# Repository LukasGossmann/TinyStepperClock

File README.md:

**Description:**  
Tiny stepper motor based clock (including base, L=80mm, W=80mm, H=127mm)  
The clock face is 50mm in diameter with a 5mm wide clear / slightly opaque ring around it for a total diameter of 60mm.  
Behind the clock face is an LED ring with 12 WS2812 LEDs that light up every hour and play a short animation.  
The stepper motors used in this clock are very weak so a lot of care need to be taken to align the shafts properly and for the gears to be running as true as possible on the shafts.  
Each stepper motor has 20 fullsteps per revolution which with a gear reduction of 3:1 gives 60 steps per revolution.  
The minute hand takes a step every minute while the hour hand takes a step every 12 minutes.  
Since this is the tiny version that implies the existence of a bigger stepper motor based clock.
The bigger version can be found here: [StepperClock](https://github.com/LukasGossmann/StepperClock)  
**Waring:** The clock is mains powered and there are a few somewhat exposed live traces / metal contacts so build and use at your own risk.

**Building:**  
Create all parts needed as shown in the FreeCAD drawing.  
Assemble as shown on the pictures and in the FreeCAD drawing.  
A lot of care needs to be taken to be as precise as possible as there isn't much room for tolerance in this design due to the weak motors and tiny gears.  
Also a lot of parts are press fit together (bearings in holders, motors in holders, clock face in clear ring, clear ring on LED ring, etc.) so make sure to adjust the design to fit the expacted tolerances of your manufacturing process and the parts you bought.
Note that one of the stepper motors is wired in the opposite direction so that the same step sequence can be used to drive them.  
If the motors are turning in the wrong direction or both motors were wired the same on accident the code allows for inverting the motor direction as well.
When attaching the clock hands to the shaft the clock needs to be powered on (preferably through usb).  
That way the stepper motors align with one of their magnetic steps which ensures that the hands can properly point to all positions they need to.
Align the clock hands with the 12 o'clock position and solder them in place.

**Tools:**
- **CNC machine** or other way to create parts from a piece of flat material as well as for engraving the clock face.
- **FDM or SLA printer** to create the spacer and the clear ring.
- Depending on the parts you can get and the need to modify them a **lathe** is very useful.
- Soldering iron, screwdrivers, etc.

**Stepper motors:**  
20 steps per rev  
3.3V @ 80mA per coil (gets slightly warm)  
Does not like having both coils energized at the same time, gets pretty hot and doesn't step well  
Diameter: 8mm  
Length: 9.2mm  
Gear (from factory): 10 teeth 0.2 module? (2.3mm diameter)  
Can be found from multiple sellers in china for very cheap (AliExpress)

**Stepper driver:**  
DRV8833 without current limiting (3.3V straight through)  
On a breakout board just soldered onto carrier PCB

**Clock hands:**  
Need to be made of a material that can be soldered to so they can be attached to the shafts.  
CNC milling them from some leftover PCB material works great.

**Power supply:**  
The Pi Pico is powered from a 230V to 5V mains power supply "brick" made by Hi-Link which can supply 600mA.  
To power the stepper drivers the 3.3V output of the Pi Pico is used. 
The stepper motors together draw around 160mA at 3.3V with only one of their coils being active at a time.

**Needed parts (mechanical):**
- 2x 60 tooth gear, 1.4mm thick, 0.3 module
    - one with 4mm hole and one with 2mm hole for the shaft
- 2x 20 tooth gear, 1.4mm thick, 0.3 module
    - with 2.3mm hole to fit onto factory gear of the stepper motor
- 2x Bearing 8mm OD, 4mm ID, 3mm thick
- 1x Bearing 7.3mm OD, 2mm ID, 3mm thick
    - 7mm OD bearings are also available, pick whatever is cheaper and modify the bearing holder design to fit your needs
- 3mm thick material for the frame parts (I used Resopal)
- Brass tube 4mm OD, 2mm ID (shaft for the hour hand)
- Brass tube 5mm OD, 3mm ID (used as spacers for the stacked PCBs)
- Brass rod 2mm (shaft for the minute hand)
- Various M2 and M3 screws, nuts and washers
- A block of wood or other material to make a base for the clock

**Needed parts (electrical):**
- 2x Stepper motor
    - order more than that because they tend to arrive broken (coil wires ripped off)
- 1x Raspberry Pi Pico without headers
- 1x 5V PSU (Hi-Link HLK-PM01 or pin and size compatible)
- 1x WS2812 LED ring with 12 LEDS (~50mm OD)
    - 8 LED version (~32mm OD) should work too with a modified spacer and a few code changes
- 1x Diode (shotkey or any other type, 1N4007 works just fine)
- 1x Capacitor (At least 5V rating, around 470µF works fine)
- 1x 2.54mm 2 pin screw terminal
- Some 2.54mm pin headers
- Thin wires
- The PCBs from the KiCAD project

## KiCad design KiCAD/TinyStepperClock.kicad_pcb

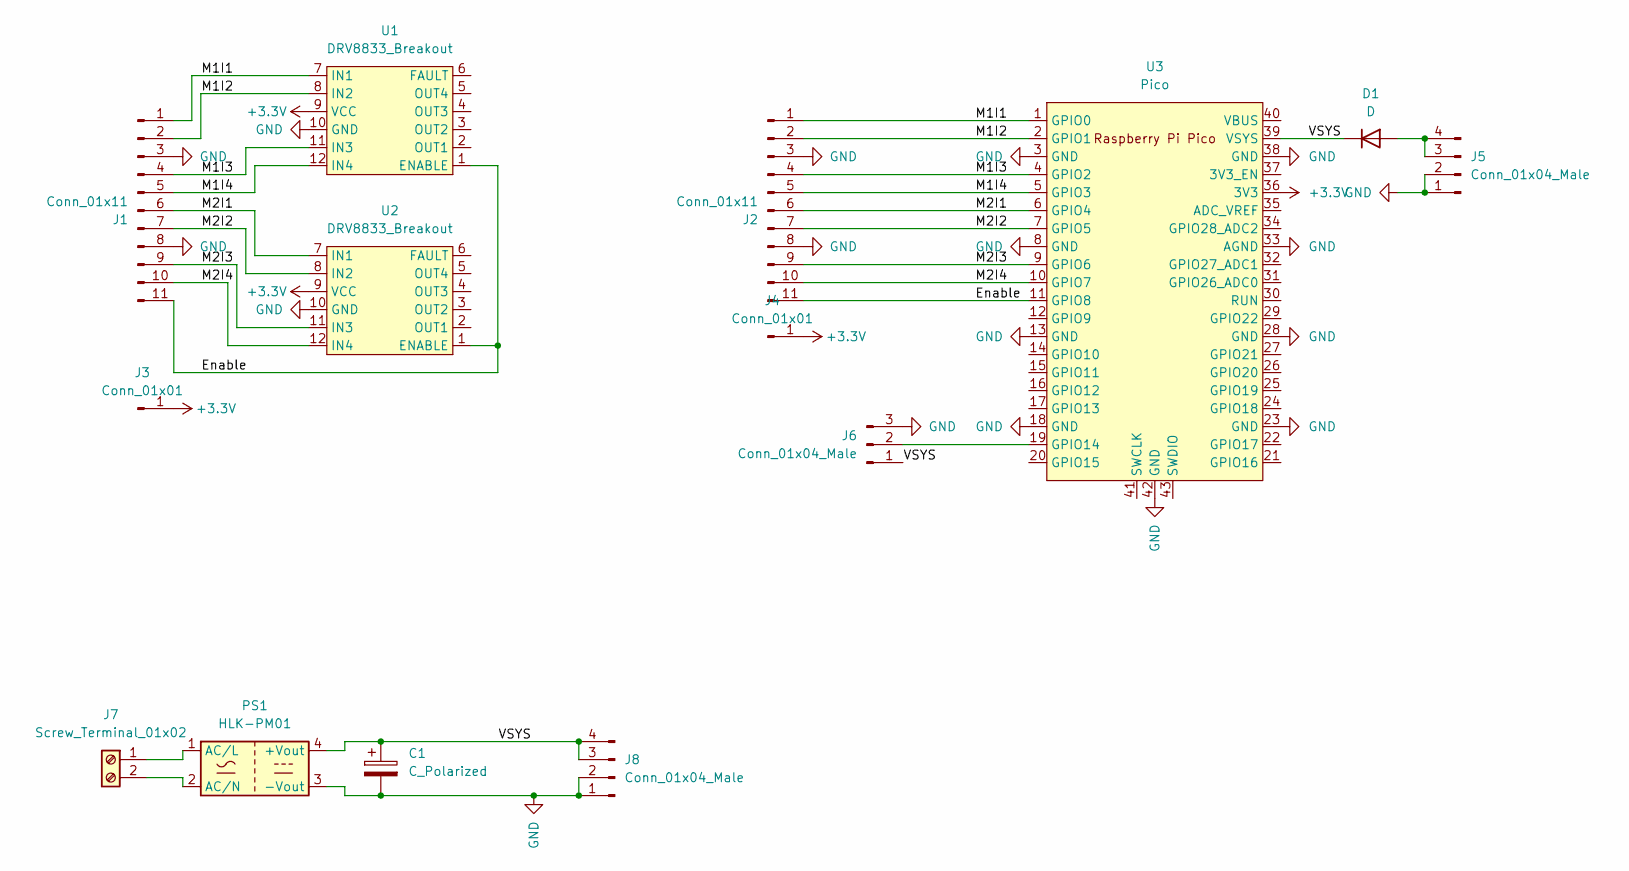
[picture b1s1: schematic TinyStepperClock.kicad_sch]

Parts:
C1: C_Polarized; CP_Radial_D10.0mm_P5.00mm_P7.50mm
D1: D; D_DO-15_P12.70mm_Horizontal
J1, J2: Conn_01x11; PinHeader_1x11_P2.54mm_Vertical
J3, J4: Conn_01x01; PinHeader_1x01_P2.54mm_Vertical
J5: Conn_01x04_Male; PinHeader_1x04_P2.54mm_Vertical
J6: Conn_01x04_Male; PinHeader_1x03_P2.54mm_Horizontal
J7: Screw_Terminal_01x02; TerminalBlock_Phoenix_MKDS-1,5-2-5.08_1x02_P5.08mm_Horizont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
J8: Conn_01x04_Male; PinSocket_1x04_P2.54mm_Vertical
PS1: HLK-PM01; Converter_ACDC_HiLink_HLK-PMxx
U1, U2: DRV8833_Breakout
U3: Pico; RPi_Pico_SMD_TH

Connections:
+3.3V: J3.1, J4.1, U1.9 (VCC), U2.9 (VCC), U3.36 (3V3)
/Enable: J1.11, J2.11, U1.1 (ENABLE), U2.1 (ENABLE), U3.11 (GPIO8)
/M1I1: J1.1, J2.1, U1.7 (IN1), U3.1 (GPIO0)
/M1I2: J1.2, J2.2, U1.8 (IN2), U3.2 (GPIO1)
/M1I3: J1.4, J2.4, U1.11 (IN3), U3.4 (GPIO2)
/M1I4: J1.5, J2.5, U1.12 (IN4), U3.5 (GPIO3)
/M2I1: J1.6, J2.6, U2.7 (IN1), U3.6 (GPIO4)
/M2I2: J1.7, J2.7, U2.8 (IN2), U3.7 (GPIO5)
/M2I3: J1.9, J2.9, U2.11 (IN3), U3.9 (GPIO6)
/M2I4: J1.10, J2.10, U2.12 (IN4), U3.10 (GPIO7)
/VSYS: C1.1, D1.1 (K), J6.1, J8.3, J8.4, PS1.4 (+Vout), U3.39 (VSYS)
GND: C1.2, J1.3, J1.8, J2.3, J2.8, J5.1, J5.2, J6.3, J8.1, J8.2, PS1.3 (-Vout), U1.10 (GND), U2.10 (GND), U3.3 (GND), U3.8 (GND), U3.13 (GND), U3.18 (GND), U3.23 (GND), U3.28 (GND), U3.33 (AGND), U3.38 (GND), U3.42 (GND)
unnamed: D1.2 (A), J5.3, J5.4
unnamed: J6.2, U3.19 (GPIO14)
unnamed: J7.1, PS1.1 (AC/L)
unnamed: J7.2, PS1.2 (AC/N)

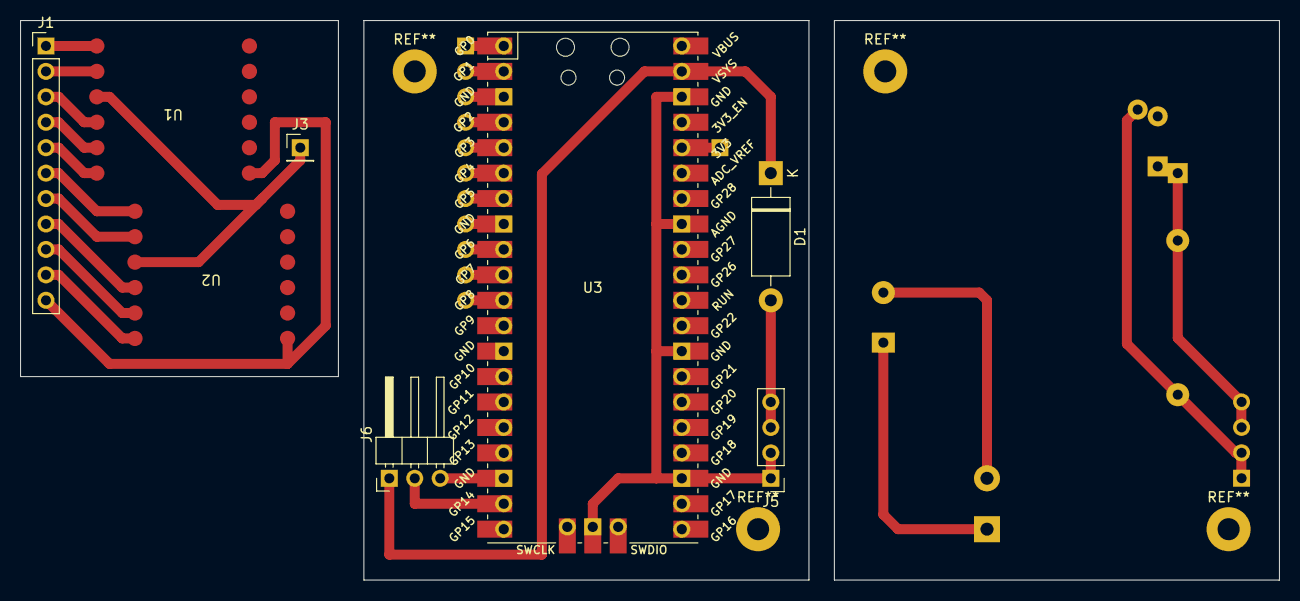
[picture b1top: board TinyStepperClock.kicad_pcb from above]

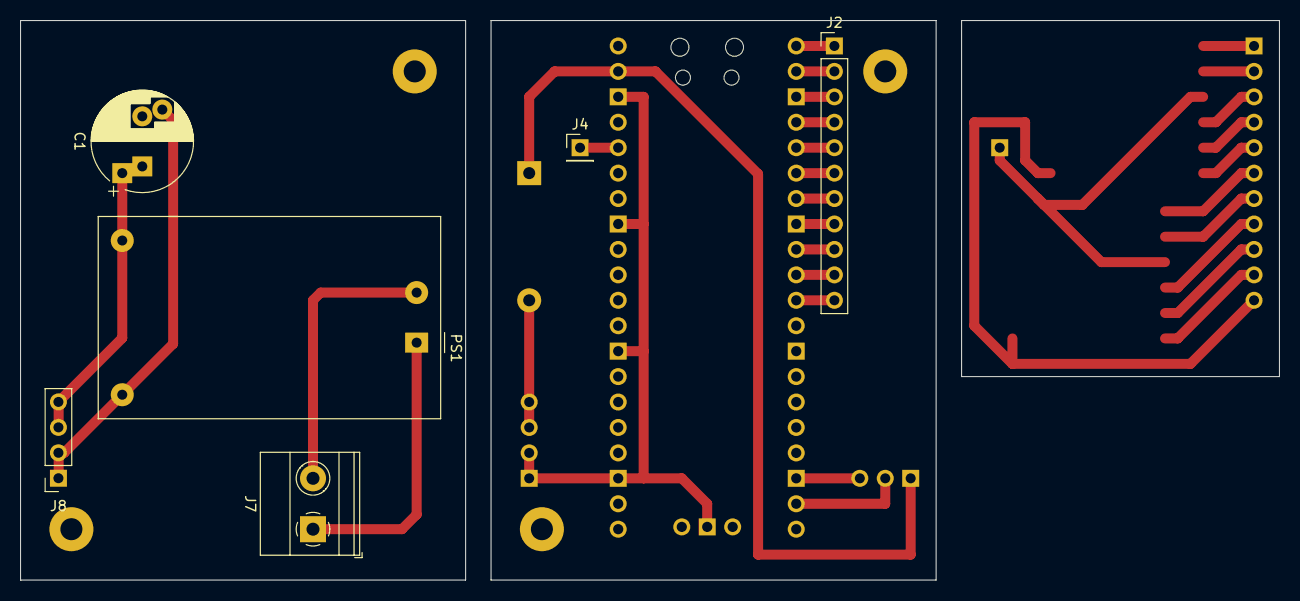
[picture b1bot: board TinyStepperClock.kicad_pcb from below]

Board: 2 copper layers, 125.7 x 55.9 mm, 14 parts (6 on the bottom side), 16 nets.

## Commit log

2022-12-28 Lots of cleanup
2023-01-02 Fixed bug where clock hands would move while setting the time and cad model updates
2023-02-02 Readded missing update of rtc alarm
2023-11-11 Updated readme file
